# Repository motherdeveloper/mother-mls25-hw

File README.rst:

=====================
Mother MLS12 hardware
=====================

A 12W tunable-white LED driver, powered via PoE.

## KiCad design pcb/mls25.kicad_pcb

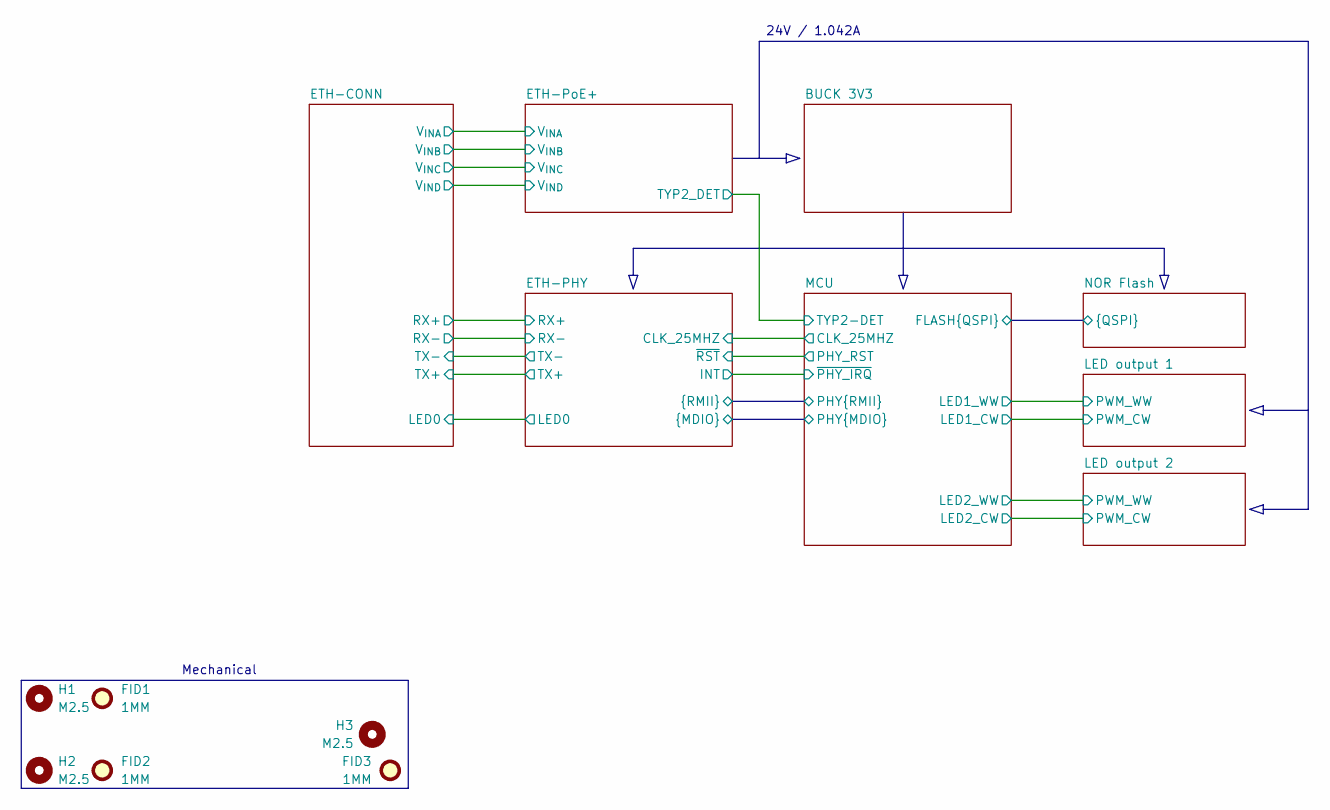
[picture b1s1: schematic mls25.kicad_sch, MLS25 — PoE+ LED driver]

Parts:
FID1, FID2, FID3: 1MM; Fiducial_1mm_Mask2mm
H1, H2, H3: M2.5; MountingHole_2.7mm_M2.5_ISO7380

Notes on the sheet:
24V / 1.042A
Mechanical

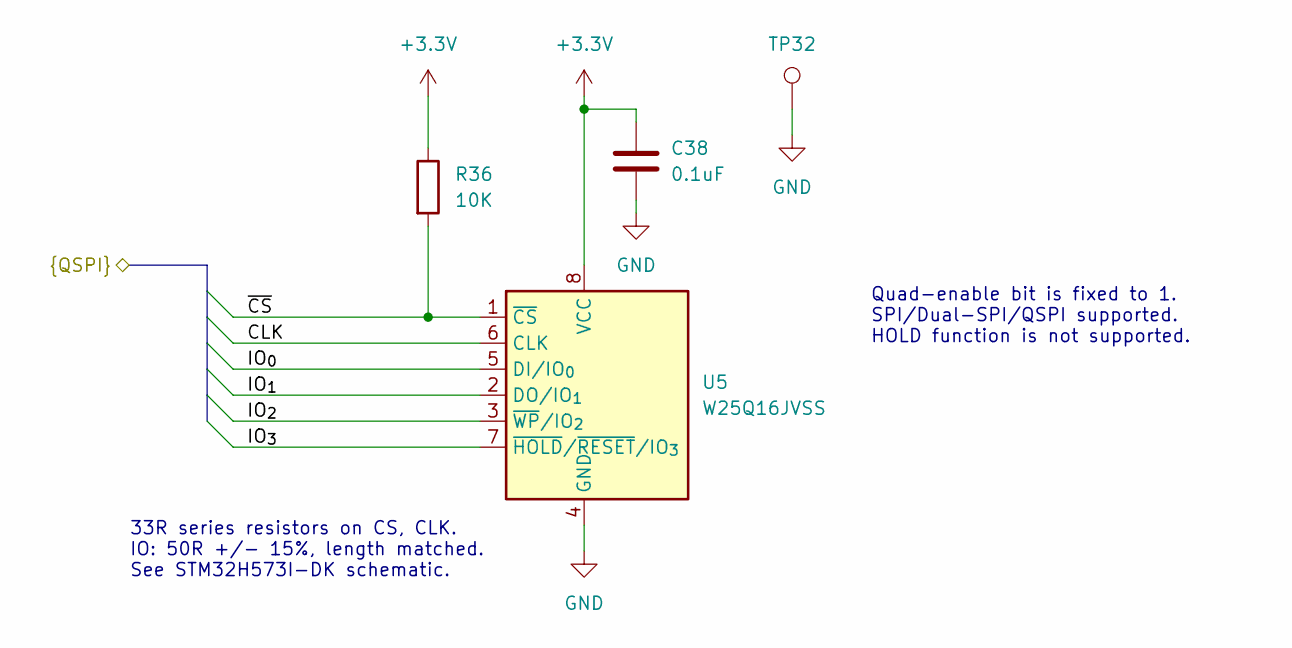
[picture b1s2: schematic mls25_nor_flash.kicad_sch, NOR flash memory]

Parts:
C38: 0.1uF; C_0603_1608Metric; MPN C0603C104M5RACAUTO
R36: 10K; R_0603_1608Metric; MPN AF0603FR-0710KL
TP32: TestPoint; TestPoint_Pad_1.5x1.5mm
U5: W25Q16JVSS; SOIC-8_5.3x5.3mm_P1.27mm; MPN W25Q16JVSSIQ

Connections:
+3.3V: C38.1, R36.1, U5.8 (VCC); also elsewhere on the board
/MCU/FLASH.CLK: U5.6 (CLK); also elsewhere on the board
/MCU/FLASH.IO_{0}: U5.5 (DI/IO_{0}); also elsewhere on the board
/MCU/FLASH.IO_{1}: U5.2 (DO/IO_{1}); also elsewhere on the board
/MCU/FLASH.IO_{2}: U5.3 (~WP/IO_{2}); also elsewhere on the board
/MCU/FLASH.IO_{3}: U5.7 (~HOLD/~RESET/IO_{3}); also elsewhere on the board
/MCU/FLASH.~CS: R36.2, U5.1 (~CS); also elsewhere on the board
GND: C38.2, TP32.1, U5.4 (GND); also elsewhere on the board

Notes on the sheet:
33R series resistors on CS, CLK. IO: 50R +/- 15%, length matched. See STM32H573I-DK schematic.
Quad-enable bit is fixed to 1. SPI/Dual-SPI/QSPI supported. HOLD function is not supported.

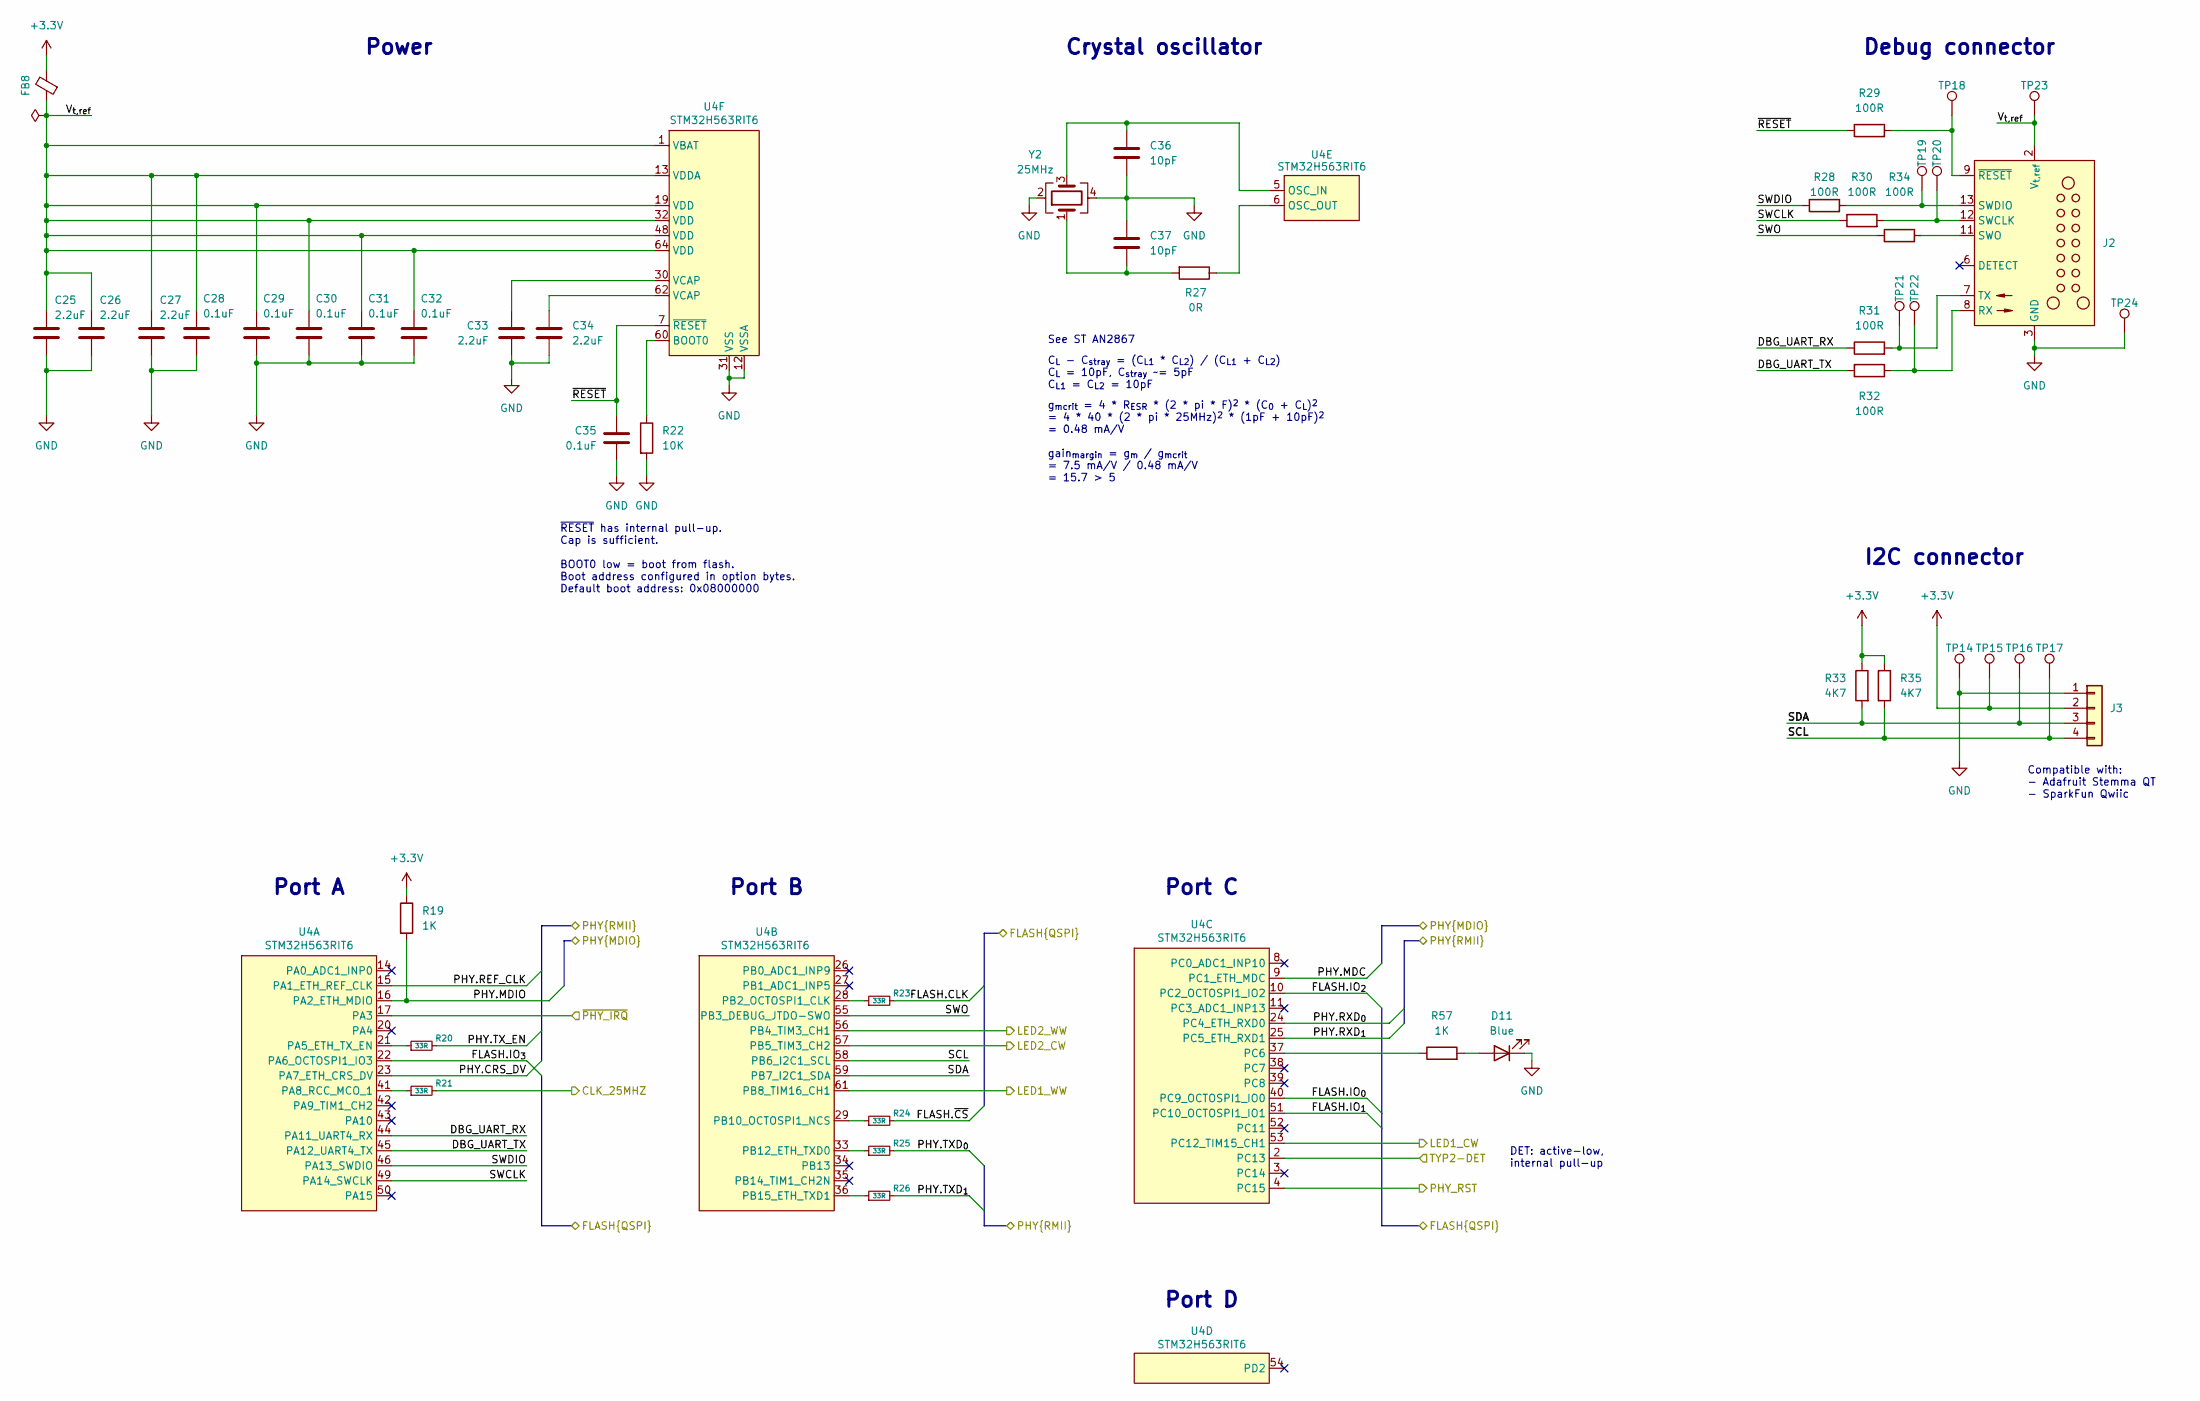
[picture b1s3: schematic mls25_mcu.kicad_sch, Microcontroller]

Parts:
C25, C26, C27, C33, C34: 2.2uF; C_0603_1608Metric; MPN CL10A225KQ8NNNC
C28, C29, C30, C31, C32, C35: 0.1uF; C_0603_1608Metric; MPN C0603C104M5RACAUTO
C36, C37: 10pF; C_0603_1608Metric; MPN 0603N100J100CT
D11: Blue; LED_0603_1608Metric; MPN LTST-C193TBKT-5A
FB8: FerriteBead_Small; L_0805_2012Metric; MPN MPZ2012S102AT000
J2: TC2070-FP; Tag-Connect_TC2070-IDC-FP_2x07_P1.27mm_Vertical; MPN TC2070-IDC-FP
J3: SM04B-SRSS-TB; JST_SH_SM04B-SRSS-TB_1x04-1MP_P1.00mm_Horizontal; MPN SM04B-SRSS-TB
R19, R57: 1K; R_0603_1608Metric; MPN AC0603JR-131KL
R20, R21, R23, R24, R25, R26: 33R; R_0603_1608Metric; MPN WR06X330 JTL
R22: 10K; R_0603_1608Metric; MPN AF0603FR-0710KL
R27: 0R; R_0603_1608Metric; MPN RC0603JR-100RL
R28, R29, R30, R31, R32, R34: 100R; R_0603_1608Metric; MPN RC0603JR-10100RL
R33, R35: 4K7; R_0603_1608Metric; MPN RC0603JR-134K7L
TP14, TP24: TestPoint; TestPoint_Pad_1.5x1.5mm
TP15, TP16, TP17, TP18, TP19, TP20, TP21, TP22, TP23: TestPoint; TestPoint_Pad_D1.5mm
U4: STM32H563RIT6; LQFP-64_10x10mm_P0.5mm; MPN STM32H563RIT6
Y2: 25MHz; Crystal_SMD_3225-4Pin_3.2x2.5mm; MPN CX3225FB25000F0FZZH1

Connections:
+3.3V: FB8.2, J3.2, R19.1, R33.1, R35.1, TP15.1; also elsewhere on the board
/ETH-PHY/CLK_25MHZ: R21.2; also elsewhere on the board
/ETH-PHY/CRS_DV: U4.23 (PA7_ETH_CRS_DV); also elsewhere on the board
/ETH-PHY/INT: U4.17 (PA3); also elsewhere on the board
/ETH-PHY/MDC: U4.9 (PC1_ETH_MDC); also elsewhere on the board
/ETH-PHY/MDIO: R19.2, U4.16 (PA2_ETH_MDIO); also elsewhere on the board
/ETH-PHY/REF_CLK: U4.15 (PA1_ETH_REF_CLK); also elsewhere on the board
/ETH-PHY/RXD_{0}: U4.24 (PC4_ETH_RXD0); also elsewhere on the board
/ETH-PHY/RXD_{1}: U4.25 (PC5_ETH_RXD1); also elsewhere on the board
/ETH-PHY/TXD_{0}: R25.2; also elsewhere on the board
/ETH-PHY/TXD_{1}: R26.2; also elsewhere on the board
/ETH-PHY/TX_EN: R20.2; also elsewhere on the board
/ETH-PHY/~RST: U4.4 (PC15); also elsewhere on the board
/ETH-PoE+/TYP2_DET: U4.2 (PC13); also elsewhere on the board
/LED output 1/PWM_CW: U4.53 (PC12_TIM15_CH1); also elsewhere on the board
/LED output 1/PWM_WW: U4.61 (PB8_TIM16_CH1); also elsewhere on the board
/LED output 2/PWM_CW: U4.57 (PB5_TIM3_CH2); also elsewhere on the board
/LED output 2/PWM_WW: U4.56 (PB4_TIM3_CH1); also elsewhere on the board
/MCU/DBG_UART_RX: R31.1, U4.44 (PA11_UART4_RX)
/MCU/DBG_UART_TX: R32.2, U4.45 (PA12_UART4_TX)
/MCU/FLASH.CLK: R23.2; also elsewhere on the board
/MCU/FLASH.IO_{0}: U4.40 (PC9_OCTOSPI1_IO0); also elsewhere on the board
/MCU/FLASH.IO_{1}: U4.51 (PC10_OCTOSPI1_IO1); also elsewhere on the board
/MCU/FLASH.IO_{2}: U4.10 (PC2_OCTOSPI1_IO2); also elsewhere on the board
/MCU/FLASH.IO_{3}: U4.22 (PA6_OCTOSPI1_IO3); also elsewhere on the board
/MCU/FLASH.~CS: R24.2; also elsewhere on the board
/MCU/SCL: J3.4, R35.2, TP17.1, U4.58 (PB6_I2C1_SCL)
/MCU/SDA: J3.3, R33.2, TP16.1, U4.59 (PB7_I2C1_SDA)
/MCU/SWCLK: R30.1, U4.49 (PA14_SWCLK)
/MCU/SWDIO: R28.1, U4.46 (PA13_SWDIO)
/MCU/SWO: R34.1, U4.55 (PB3_DEBUG_JTDO-SWO)
/MCU/V_{t,ref}: C25.1, C26.1, C27.1, C28.1, C29.1, C30.1, C31.1, C32.1, FB8.1, J2.2 (V_{t,ref}), TP23.1, U4.1 (VBAT), U4.13 (VDDA), U4.19 (VDD), U4.32 (VDD), U4.48 (VDD), U4.64 (VDD)
/MCU/~RESET: C35.1, R29.1, U4.7 (~RESET)
GND: C25.2, C26.2, C27.2, C28.2, C29.2, C30.2, C31.2, C32.2, C33.2, C34.2, C35.2, C36.2, C37.1, D11.1 (K), J2.3 (GND), J2.4 (GND), J3.1, R22.2, TP14.1, TP24.1, U4.12 (VSSA), U4.18 (VSSA), U4.31 (VSS), U4.47 (VSS), U4.63 (VSS), Y2.2, Y2.4; also elsewhere on the board
unnamed: C33.1, U4.30 (VCAP)
unnamed: C34.1, U4.62 (VCAP)
unnamed: C37.2, R27.2, Y2.1
unnamed: D11.2 (A), R57.2
unnamed: J2.8 (RX), R32.1, TP22.1
unnamed: J2.12 (SWCLK), R30.2, TP20.1
unnamed: J2.13 (SWDIO), R28.2, TP19.1
unnamed: J2.11 (SWO), R34.2
unnamed: J2.7 (TX), R31.2, TP21.1
unnamed: J2.9 (~RESET), R29.2, TP18.1
unnamed: R20.1, U4.21 (PA5_ETH_TX_EN)
unnamed: R21.1, U4.41 (PA8_RCC_MCO_1)
unnamed: R23.1, U4.28 (PB2_OCTOSPI1_CLK)
unnamed: R24.1, U4.29 (PB10_OCTOSPI1_NCS)
unnamed: R25.1, U4.33 (PB12_ETH_TXD0)
unnamed: R26.1, U4.36 (PB15_ETH_TXD1)
unnamed: R57.1, U4.37 (PC6)
unnamed: C36.1, U4.5 (OSC_IN), Y2.3
unnamed: R27.1, U4.6 (OSC_OUT)
unnamed: R22.1, U4.60 (BOOT0)

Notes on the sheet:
C_{L} - C_{stray} = (C_{L1} * C_{L2}) / (C_{L1} + C_{L2}) C_{L} = 10pF, C_{stray} ~= 5pF C_{L1} = C_{L2} = 10pF
See ST AN2867
I2C connector
g_{mcrit} = 4 * R_{ESR} * (2 * pi * F)^{2} * (C_{0} + C_{L})^{2} = 4 * 40 * (2 * pi * 25MHz)^{2} * (1pF + 10pF)^{2} = 0.48 mA/V gain_{margin} = g_{m} / g_{mcrit} = 7.5 mA/V / 0.48 mA/V = 15.7 > 5
Debug connector
Crystal oscillator
Power
Port A
Compatible with: - Adafruit Stemma QT - SparkFun Qwiic
Port D
Port C
Port B
DET: active-low, internal pull-up
~{RESET} has internal pull-up. Cap is sufficient. BOOT0 low = boot from flash. Boot address configured in option bytes. Default boot address: 0x08000000

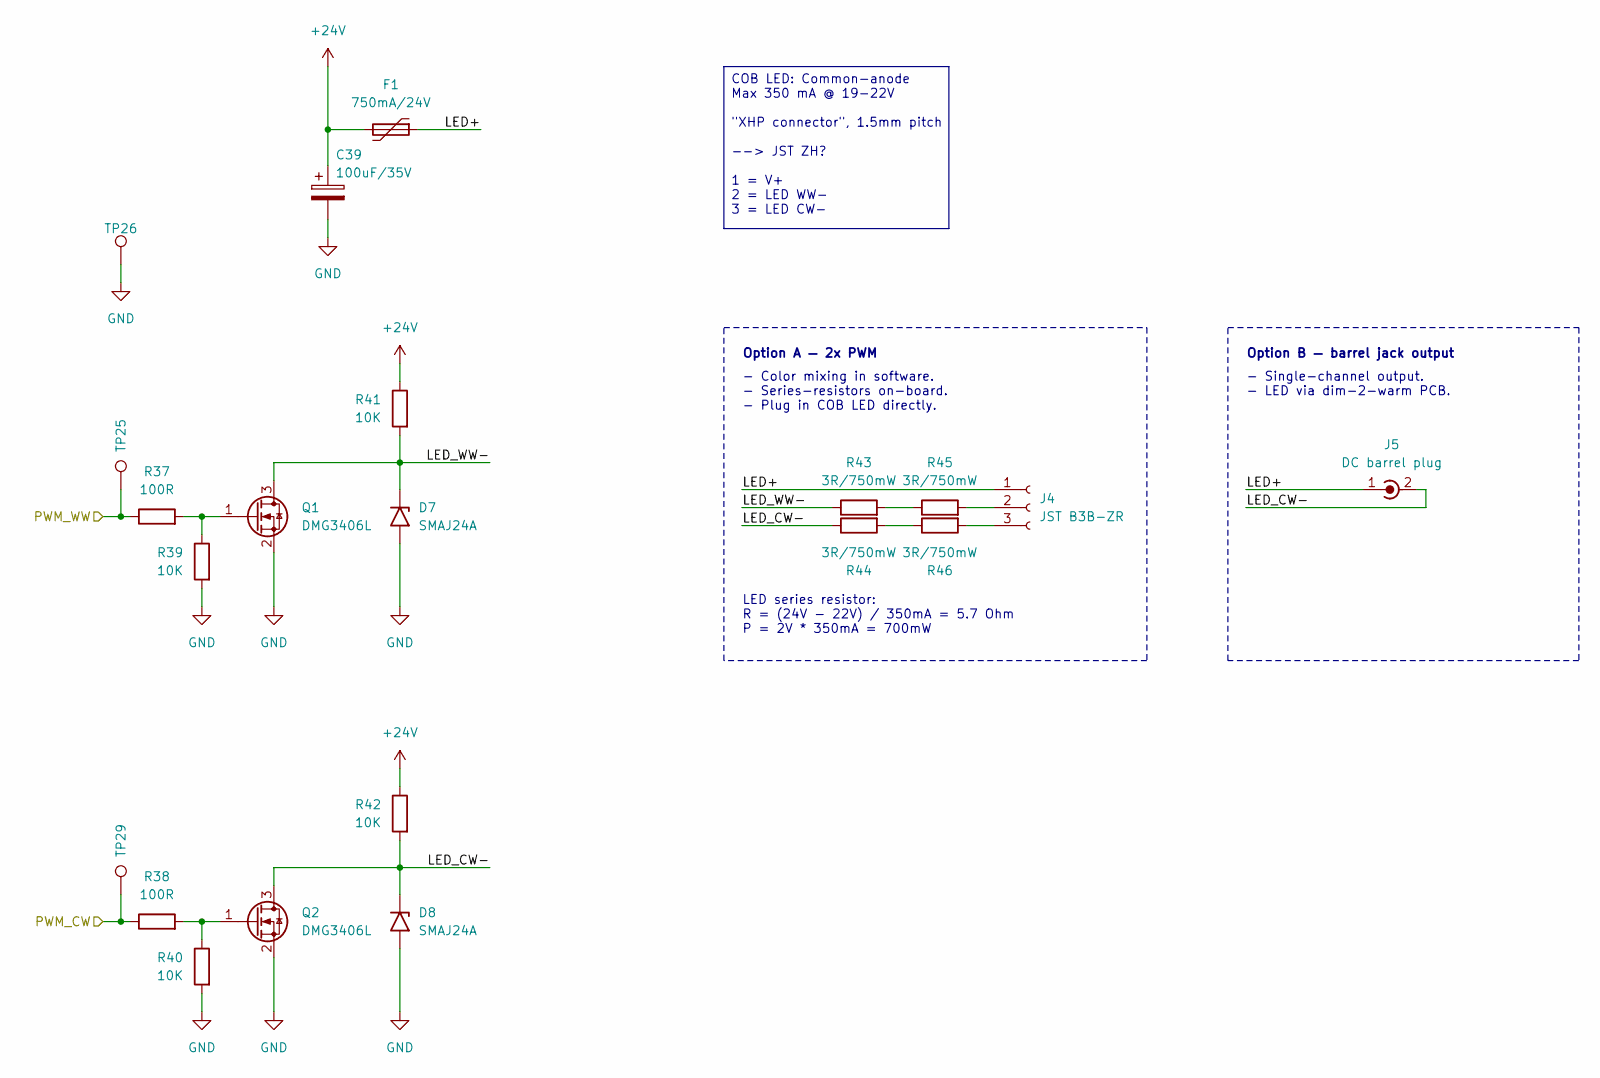
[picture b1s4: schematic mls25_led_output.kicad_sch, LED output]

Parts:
C39: 100uF/35V; CP_Elec_6.3x5.9; MPN 865080545012
D7, D8: SMAJ24A; D_SMA; MPN SMBJ24A/TR13
F1: 750mA/24V; SMD1812B050TF_30; MPN SMD1812B075TF/24
J4: JST B3B-ZR; JST_ZH_B3B-ZR_1x03_P1.50mm_Vertical; MPN B3B-ZR
J5: DC barrel plug; DC_Barrel_Plug_2.1x5.5mm
Q1, Q2: DMG3406L; SOT-23; MPN DMG3406L-13
R37, R38: 100R; R_0603_1608Metric; MPN RC0603JR-10100RL
R39, R40, R41, R42: 10K; R_0603_1608Metric; MPN AF0603FR-0710KL
R43, R44, R45, R46: 3R/750mW; R_1206_3216Metric; MPN ESR18EZPF3R00
TP25, TP29: TestPoint; TestPoint_Pad_D1.5mm
TP26: TestPoint; TestPoint_Pad_1.5x1.5mm

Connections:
+24V: C39.1, F1.2, R41.1, R42.1; also elsewhere on the board
/LED output 1/LED+: F1.1, J4.1, J5.1 (In)
/LED output 1/LED_CW-: D8.1 (A1), J5.2 (Ext), Q2.3 (D), R42.2, R44.1
/LED output 1/LED_WW-: D7.1 (A1), Q1.3 (D), R41.2, R43.1
/LED output 1/PWM_CW: R38.1, TP29.1; also elsewhere on the board
/LED output 1/PWM_WW: R37.1, TP25.1; also elsewhere on the board
GND: C39.2, D7.2 (A2), D8.2 (A2), Q1.2 (S), Q2.2 (S), R39.2, R40.2, TP26.1; also elsewhere on the board
unnamed: J4.2, R45.2
unnamed: J4.3, R46.2
unnamed: Q1.1 (G), R37.2, R39.1
unnamed: Q2.1 (G), R38.2, R40.1
unnamed: R43.2, R45.1
unnamed: R44.2, R46.1

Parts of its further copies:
C40: 100uF/35V; CP_Elec_6.3x5.9; MPN 865080545012
D9, D10: SMAJ24A; D_SMA; MPN SMBJ24A/TR13
F2: 750mA/24V; SMD1812B050TF_30; MPN SMD1812B075TF/24
J6: JST B3B-ZR; JST_ZH_B3B-ZR_1x03_P1.50mm_Vertical; MPN B3B-ZR
J7: DC barrel plug; DC_Barrel_Plug_2.1x5.5mm
Q3, Q4: DMG3406L; SOT-23; MPN DMG3406L-13
R47, R48: 100R; R_0603_1608Metric; MPN RC0603JR-10100RL
R49, R50, R51, R52: 10K; R_0603_1608Metric; MPN AF0603FR-0710KL
R53, R54, R55, R56: 3R/750mW; R_1206_3216Metric; MPN ESR18EZPF3R00
TP27, TP30: TestPoint; TestPoint_Pad_D1.5mm
TP28: TestPoint; TestPoint_Pad_1.5x1.5mm

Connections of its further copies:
+24V: C40.1, F2.2, R51.1, R52.1; also elsewhere on the board
/LED output 2/LED+: F2.1, J6.1, J7.1 (In)
/LED output 2/LED_CW-: D10.1 (A1), J7.2 (Ext), Q4.3 (D), R52.2, R54.1
/LED output 2/LED_WW-: D9.1 (A1), Q3.3 (D), R51.2, R53.1
/LED output 2/PWM_CW: R48.1, TP30.1; also elsewhere on the board
/LED output 2/PWM_WW: R47.1, TP27.1; also elsewhere on the board
GND: C40.2, D9.2 (A2), D10.2 (A2), Q3.2 (S), Q4.2 (S), R49.2, R50.2, TP28.1; also elsewhere on the board
unnamed: J6.2, R55.2
unnamed: J6.3, R56.2
unnamed: Q3.1 (G), R47.2, R49.1
unnamed: Q4.1 (G), R48.2, R50.1
unnamed: R53.2, R55.1
unnamed: R54.2, R56.1

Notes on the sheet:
Option A — 2x PWM
- Color mixing in software. - Series-resistors on-board. - Plug in COB LED directly.
LED series resistor: R = (24V - 22V) / 350mA = 5.7 Ohm P = 2V * 350mA = 700mW
Option B — barrel jack output
- Single-channel output. - LED via dim-2-warm PCB.
COB LED: Common-anode Max 350 mA @ 19-22V "XHP connector", 1.5mm pitch --> JST ZH? 1 = V+ 2 = LED WW- 3 = LED CW-

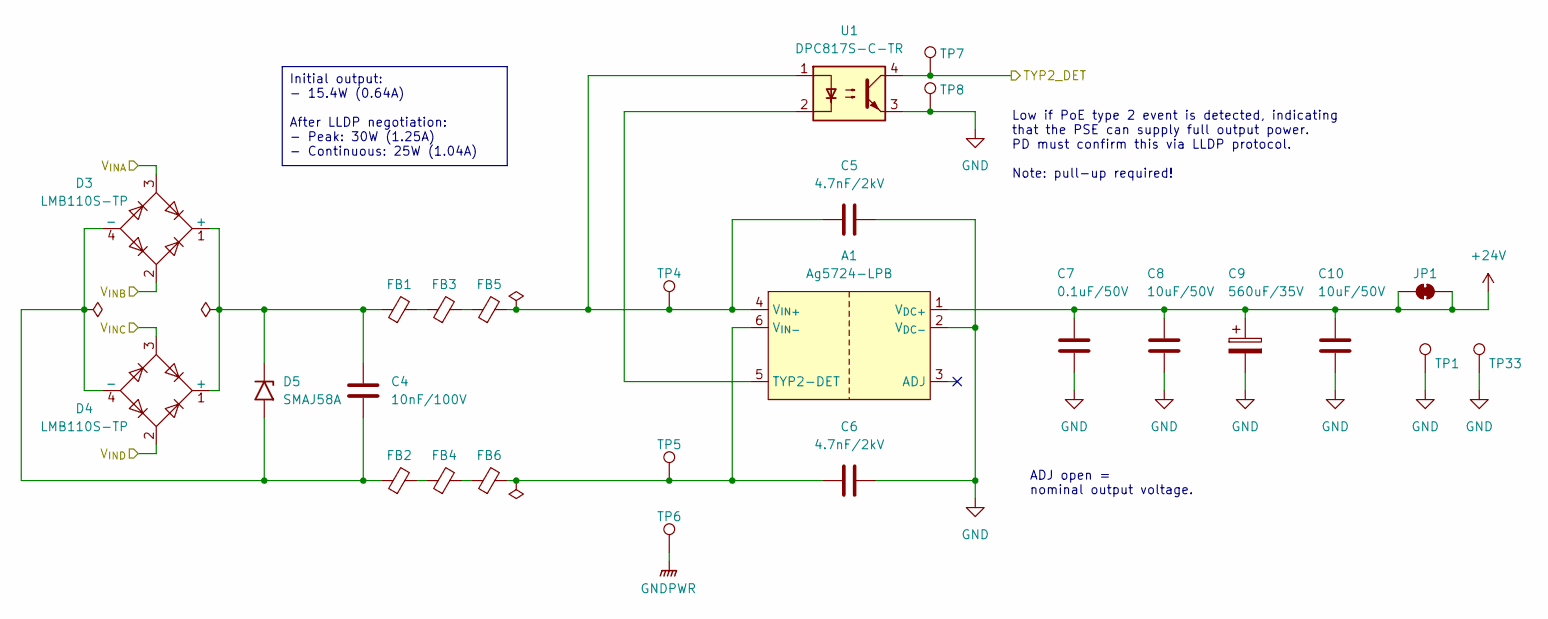
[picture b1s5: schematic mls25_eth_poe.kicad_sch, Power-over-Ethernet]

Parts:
A1: Ag5724-LPB; MPN Ag5724-LPB
C4: 10nF/100V; C_0603_1608Metric; MPN CGA3E2X7R2A103K080AA
C5, C6: 4.7nF/2kV; C_1210_3225Metric; MPN 1210B472K202CT
C7: 0.1uF/50V; C_0603_1608Metric; MPN C0603C104M5RACAUTO
C8, C10: 10uF/50V; C_1206_3216Metric; MPN 1206X106K500CT
C9: 560uF/35V; CP_Elec_10x10.5; MPN EMZS350ARA561MJA0G
D3, D4: LMB110S-TP; MPN LMB110S-TP
D5: SMAJ58A; D_SMA; MPN SMAJ58A/TR13
FB1, FB2, FB3, FB4, FB5, FB6: FerriteBead_Small; L_0805_2012Metric; MPN MPZ2012S102AT000
JP1: SolderJumper_2_Bridged; SolderJumper-2_P1.3mm_Bridged_RoundedPad1.0x1.5mm
TP1, TP6, TP8, TP33: TestPoint; TestPoint_Pad_1.5x1.5mm
TP4, TP5, TP7: TestPoint; TestPoint_Pad_D1.5mm
U1: DPC817S-C-TR; MPN DPC817S-C-TR

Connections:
+24V: A1.1 (V_{DC+}), C7.1, C8.1, C9.1, C10.1, JP1.1 (A), JP1.2 (B); also elsewhere on the board
/ETH-CONN/V_{INA}: D3.3; also elsewhere on the board
/ETH-CONN/V_{INB}: D3.2; also elsewhere on the board
/ETH-CONN/V_{INC}: D4.3; also elsewhere on the board
/ETH-CONN/V_{IND}: D4.2; also elsewhere on the board
/ETH-PoE+/TYP2_DET: TP7.1, U1.4; also elsewhere on the board
GND: A1.2 (V_{DC-}), C5.2, C6.2, C7.2, C8.2, C9.2, C10.2, TP1.1, TP8.1, TP33.1, U1.3; also elsewhere on the board
GNDPWR: TP6.1; also elsewhere on the board
unnamed: A1.5 (TYP2-DET), U1.2
unnamed: A1.4 (V_{IN+}), C5.1, FB5.2, TP4.1, U1.1
unnamed: A1.6 (V_{IN-}), C6.1, FB6.2, TP5.1
unnamed: C4.1, D3.1 (+), D4.1 (+), D5.1 (A1), FB1.1
unnamed: C4.2, D3.4 (-), D4.4 (-), D5.2 (A2), FB2.1
unnamed: FB1.2, FB3.1
unnamed: FB2.2, FB4.1
unnamed: FB3.2, FB5.1
unnamed: FB4.2, FB6.1

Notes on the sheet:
Low if PoE type 2 event is detected, indicating that the PSE can supply full output power. PD must confirm this via LLDP protocol. Note: pull-up required!
ADJ open = nominal output voltage.
Initial output: - 15.4W (0.64A) After LLDP negotiation: - Peak: 30W (1.25A) - Continuous: 25W (1.04A)

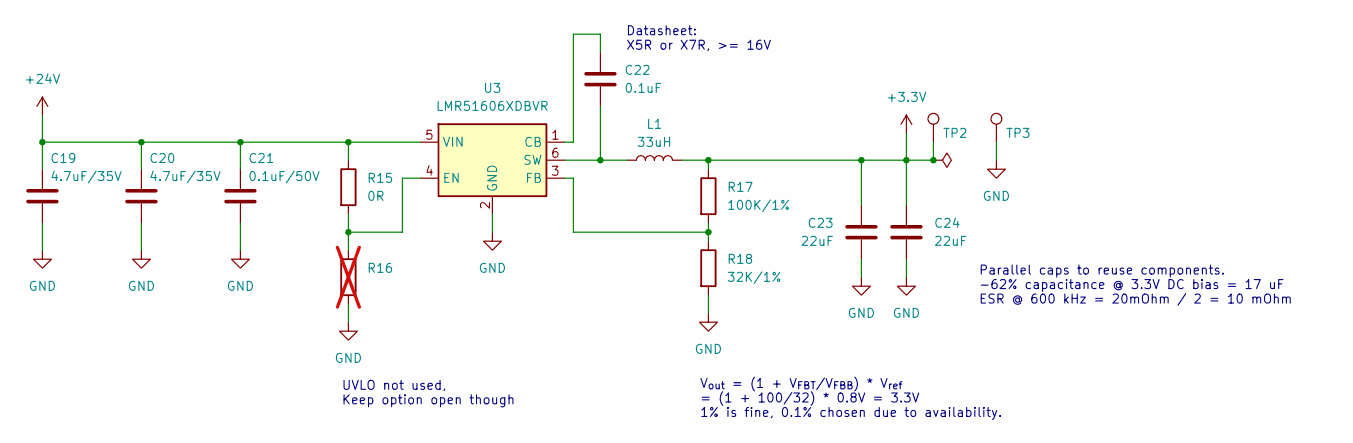
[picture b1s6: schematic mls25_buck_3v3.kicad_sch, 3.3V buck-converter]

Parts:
C19, C20: 4.7uF/35V; C_0603_1608Metric; MPN C1608X5R1V475K080AC
C21: 0.1uF/50V; C_0603_1608Metric; MPN C0603C104M5RACAUTO
C22: 0.1uF; C_0603_1608Metric; MPN C0603C104M5RACAUTO
C23, C24: 22uF; C_0603_1608Metric; MPN GRM188R60J226MEA0J
L1: 33uH; L_Taiyo-Yuden_NR-60xx; MPN NRS6045T330MMGK
R15: 0R; R_0603_1608Metric; MPN RC0603JR-100RL
R16: R_0603_1608Metric; not fitted
R17: 100K/1%; R_0603_1608Metric; MPN RT0603FRE13100KL
R18: 32K/1%; R_0603_1608Metric; MPN RT0603BRD0732KL
TP2: TestPoint; TestPoint_Pad_D1.5mm
TP3: TestPoint; TestPoint_Pad_1.5x1.5mm
U3: LMR51606XDBVR; LMR51606_SOT-23-6; MPN LMR51606XDBVR

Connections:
+3.3V: C23.1, C24.1, L1.2, R17.1, TP2.1; also elsewhere on the board
+24V: C19.1, C20.1, C21.1, R15.1, U3.5 (VIN); also elsewhere on the board
GND: C19.2, C20.2, C21.2, C23.2, C24.2, R16.2, R18.2, TP3.1, U3.2 (GND); also elsewhere on the board
unnamed: C22.1, U3.1 (CB)
unnamed: R15.2, R16.1, U3.4 (EN)
unnamed: R17.2, R18.1, U3.3 (FB)
unnamed: C22.2, L1.1, U3.6 (SW)

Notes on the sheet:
UVLO not used, Keep option open though
Parallel caps to reuse components. -62% capacitance @ 3.3V DC bias = 17 uF ESR @ 600 kHz = 20mOhm / 2 = 10 mOhm
Datasheet: X5R or X7R, >= 16V
V_{out} = (1 + V_{FBT}/V_{FBB}) * V_{ref} = (1 + 100/32) * 0.8V = 3.3V 1% is fine, 0.1% chosen due to availability.

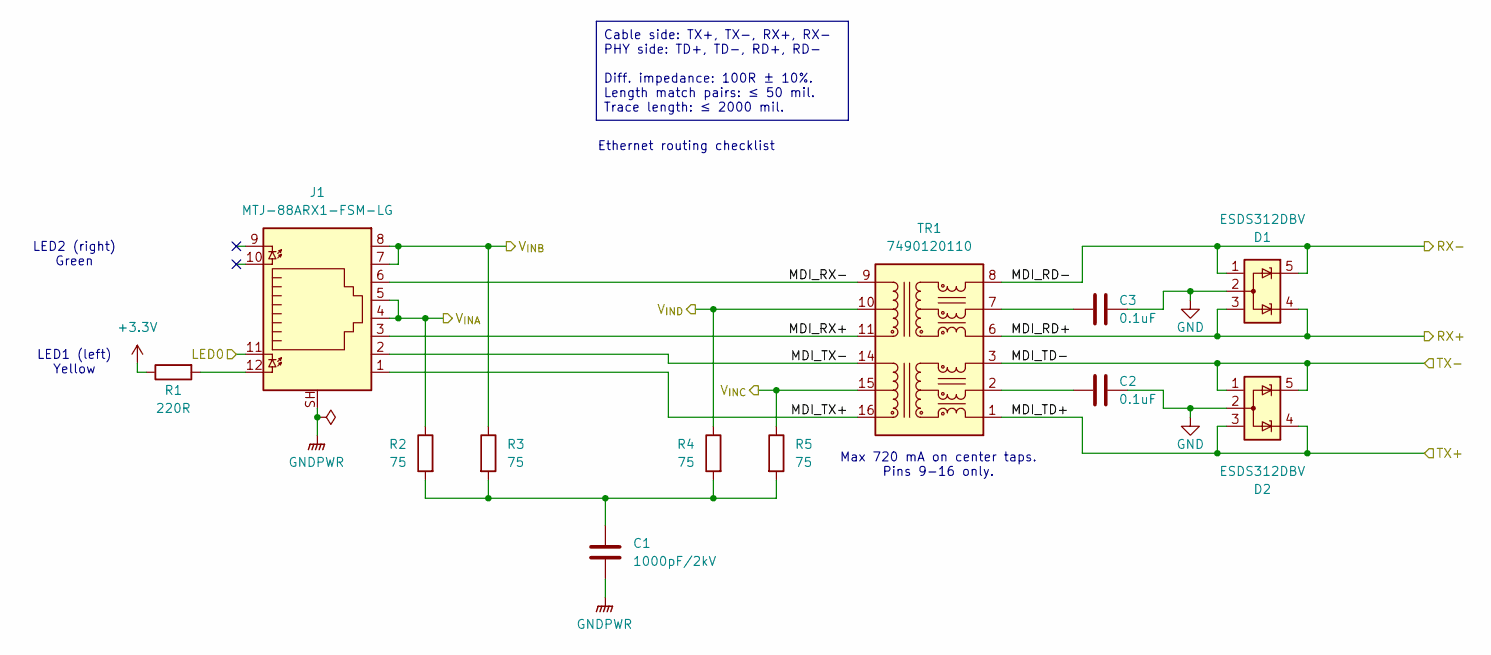
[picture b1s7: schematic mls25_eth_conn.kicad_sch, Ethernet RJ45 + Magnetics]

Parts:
C1: 1000pF/2kV; C_1206_3216Metric; MPN 885342208024
C2, C3: 0.1uF; C_0603_1608Metric; MPN C0603C104M5RACAUTO
D1, D2: ESDS312DBV; SOT-23-5; MPN ESDS312DBVR
J1: MTJ-88ARX1-FSM-LG; RJ45_Amphenol_RJHSE538X; MPN MTJ-88ARX1-FSM-LG
R1: 220R; R_0603_1608Metric; MPN RC0603JR-07220RL
R2, R3, R4, R5: 75; R_0603_1608Metric; MPN WR06X75R0FTL
TR1: 7490120110; MPN 7490120110

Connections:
+3.3V: R1.1; also elsewhere on the board
/ETH-CONN/LED0: J1.11; also elsewhere on the board
/ETH-CONN/MDI_RD+: D1.3 (NC), D1.4 (K), TR1.6 (RD+); also elsewhere on the board
/ETH-CONN/MDI_RD-: D1.1 (NC), D1.5 (K), TR1.8 (RD-); also elsewhere on the board
/ETH-CONN/MDI_RX+: J1.3, TR1.11 (RX+)
/ETH-CONN/MDI_RX-: J1.6, TR1.9 (RX-)
/ETH-CONN/MDI_TD+: D2.3 (NC), D2.4 (K), TR1.1 (TD+); also elsewhere on the board
/ETH-CONN/MDI_TD-: D2.1 (NC), D2.5 (K), TR1.3 (TD-); also elsewhere on the board
/ETH-CONN/MDI_TX+: J1.1, TR1.16 (TX+)
/ETH-CONN/MDI_TX-: J1.2, TR1.14 (TX-)
/ETH-CONN/V_{INA}: J1.4, J1.5, R2.1; also elsewhere on the board
/ETH-CONN/V_{INB}: J1.7, J1.8, R3.1; also elsewhere on the board
/ETH-CONN/V_{INC}: R5.1, TR1.15 (CTX); also elsewhere on the board
/ETH-CONN/V_{IND}: R4.1, TR1.10 (CRX); also elsewhere on the board
GND: C2.2, C3.2, D1.2 (A), D2.2 (A); also elsewhere on the board
GNDPWR: C1.2, J1.SH; also elsewhere on the board
unnamed: C1.1, R2.2, R3.2, R4.2, R5.2
unnamed: J1.12, R1.2
unnamed: C3.1, TR1.7 (CRD)
unnamed: C2.1, TR1.2 (CTD)

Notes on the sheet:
Ethernet routing checklist
Max 720 mA on center taps. Pins 9-16 only.
LED1 (left) Yellow
LED2 (right) Green
Cable side: TX+, TX-, RX+, RX- PHY side: TD+, TD-, RD+, RD- Diff. impedance: 100R ± 10%. Length match pairs: ≤ 50 mil. Trace length: ≤ 2000 mil.

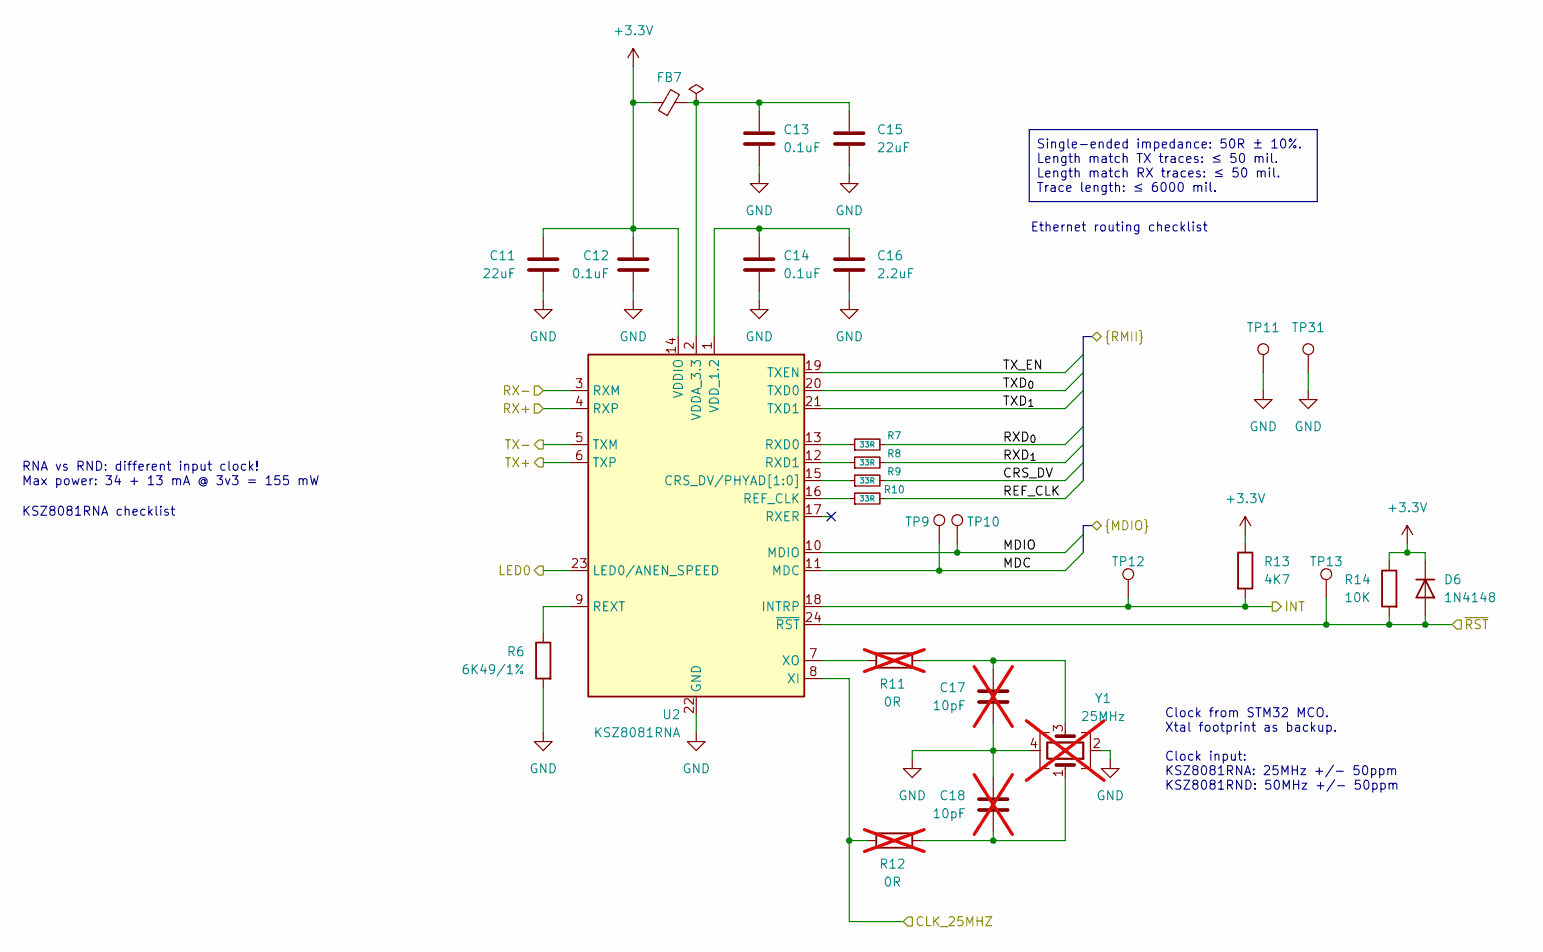
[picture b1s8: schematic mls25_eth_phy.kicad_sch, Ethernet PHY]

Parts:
C11, C15: 22uF; C_0603_1608Metric; MPN GRM188R60J226MEA0J
C12, C13, C14: 0.1uF; C_0603_1608Metric; MPN C0603C104M5RACAUTO
C16: 2.2uF; C_0603_1608Metric; MPN CL10A225KQ8NNNC
C17, C18: 10pF; C_0603_1608Metric; MPN 0603N100J100CT; not fitted
D6: 1N4148; D_SOD-523; MPN 1N4148WT
FB7: FerriteBead_Small; L_0805_2012Metric; MPN MPZ2012S102AT000
R6: 6K49/1%; R_0603_1608Metric; MPN CR0603-FX-6491ELF
R7, R8, R9, R10: 33R; R_0603_1608Metric; MPN WR06X330 JTL
R11, R12: 0R; R_0603_1608Metric; MPN RC0603JR-100RL; not fitted
R13: 4K7; R_0603_1608Metric; MPN RC0603JR-134K7L
R14: 10K; R_0603_1608Metric; MPN AF0603FR-0710KL
TP9, TP10, TP12, TP13: TestPoint; TestPoint_Pad_D1.5mm
TP11, TP31: TestPoint; TestPoint_Pad_1.5x1.5mm
U2: KSZ8081RNA; KSZ8081_QFN-24-1EP_4x4mm_P0.5mm_EP2.6x2.6mm; MPN KSZ8081RNACA
Y1: 25MHz; Crystal_SMD_3225-4Pin_3.2x2.5mm; MPN CX3225FB25000F0FZZH1; not fitted

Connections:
+3.3V: C11.1, C12.1, D6.1 (K), FB7.1, R13.1, R14.1, U2.14 (VDDIO); also elsewhere on the board
/ETH-CONN/LED0: U2.23 (LED0/ANEN_SPEED); also elsewhere on the board
/ETH-CONN/MDI_RD+: U2.4 (RXP); also elsewhere on the board
/ETH-CONN/MDI_RD-: U2.3 (RXM); also elsewhere on the board
/ETH-CONN/MDI_TD+: U2.6 (TXP); also elsewhere on the board
/ETH-CONN/MDI_TD-: U2.5 (TXM); also elsewhere on the board
/ETH-PHY/CLK_25MHZ: R12.1, U2.8 (XI); also elsewhere on the board
/ETH-PHY/CRS_DV: R9.2; also elsewhere on the board
/ETH-PHY/INT: R13.2, TP12.1, U2.18 (INTRP); also elsewhere on the board
/ETH-PHY/MDC: TP9.1, U2.11 (MDC); also elsewhere on the board
/ETH-PHY/MDIO: TP10.1, U2.10 (MDIO); also elsewhere on the board
/ETH-PHY/REF_CLK: R10.2; also elsewhere on the board
/ETH-PHY/RXD_{0}: R7.2; also elsewhere on the board
/ETH-PHY/RXD_{1}: R8.2; also elsewhere on the board
/ETH-PHY/TXD_{0}: U2.20 (TXD0); also elsewhere on the board
/ETH-PHY/TXD_{1}: U2.21 (TXD1); also elsewhere on the board
/ETH-PHY/TX_EN: U2.19 (TXEN); also elsewhere on the board
/ETH-PHY/~RST: D6.2 (A), R14.2, TP13.1, U2.24 (~RST); also elsewhere on the board
GND: C11.2, C12.2, C13.2, C14.2, C15.2, C16.2, C17.2, C18.1, R6.2, TP11.1, TP31.1, U2.22 (GND), U2.25 (GND), Y1.2, Y1.4; also elsewhere on the board
unnamed: C17.1, R11.2, Y1.3
unnamed: C18.2, R12.2, Y1.1
unnamed: R9.1, U2.15 (CRS_DV/PHYAD[1:0])
unnamed: R10.1, U2.16 (REF_CLK)
unnamed: R6.1, U2.9 (REXT)
unnamed: R7.1, U2.13 (RXD0)
unnamed: R8.1, U2.12 (RXD1)
unnamed: C13.1, C15.1, FB7.2, U2.2 (VDDA_3.3)
unnamed: C14.1, C16.1, U2.1 (VDD_1.2)
unnamed: R11.1, U2.7 (XO)

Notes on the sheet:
Ethernet routing checklist
RNA vs RND: different input clock! Max power: 34 + 13 mA @ 3v3 = 155 mW
Clock from STM32 MCO. Xtal footprint as backup. Clock input: KSZ8081RNA: 25MHz +/- 50ppm KSZ8081RND: 50MHz +/- 50ppm
KSZ8081RNA checklist
Single-ended impedance: 50R ± 10%. Length match TX traces: ≤ 50 mil. Length match RX traces: ≤ 50 mil. Trace length: ≤ 6000 mil.

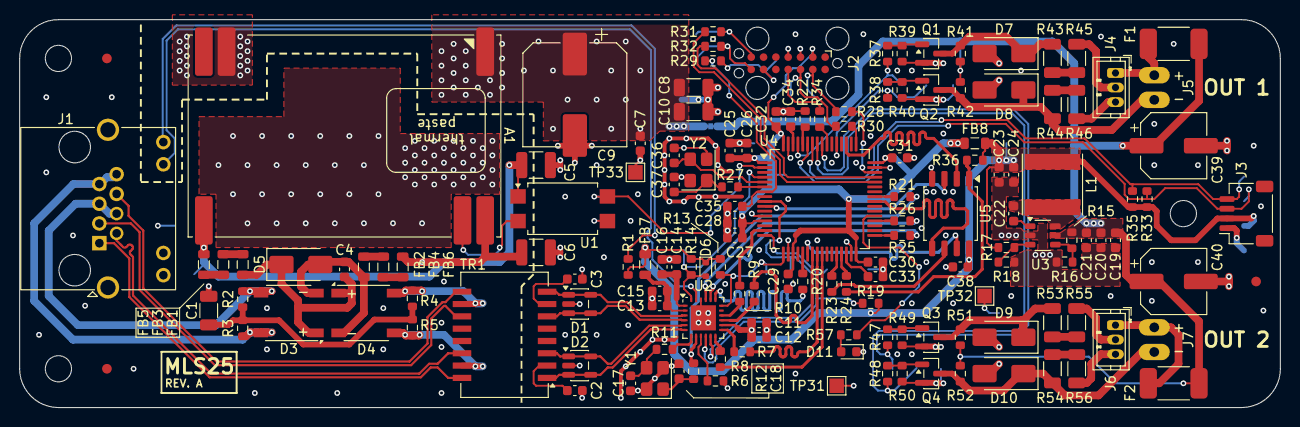
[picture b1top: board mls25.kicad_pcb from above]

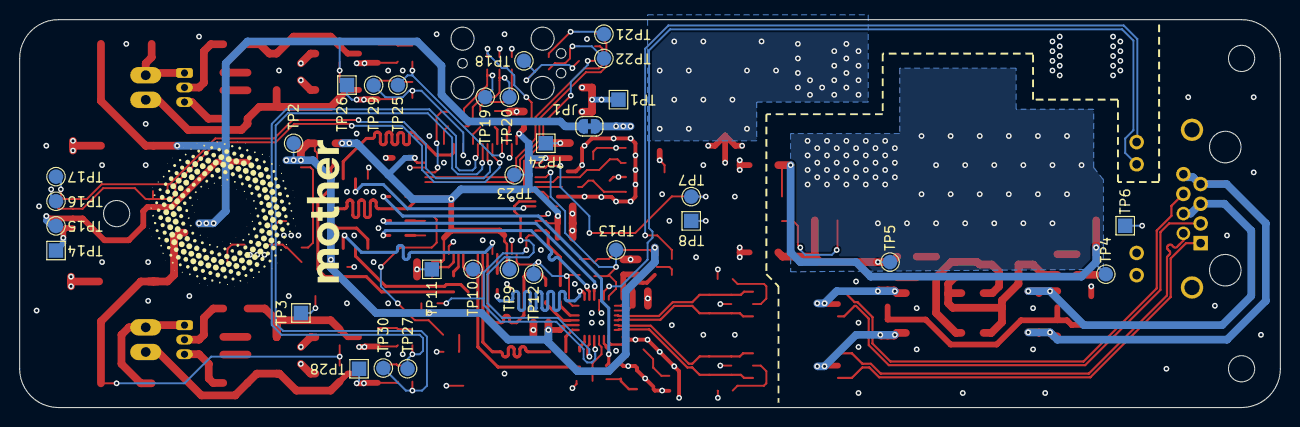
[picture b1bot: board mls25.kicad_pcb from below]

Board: 4 copper layers, 130.0 x 40.0 mm, 179 parts (31 on the bottom side), 114 nets.

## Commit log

2025-07-25 Initial version of MLS12 schematic
2025-07-26 Add LMB110S-TP bridge rectifier
2025-07-26 Add DPC817S-C-TR optocoupler
2025-07-26 Update to 25W PoE+ module, 2 outputs
2025-07-30 Fix default footprint for PoE+ magnetics
2025-07-30 Add polyfuse footprint
2025-07-31 Layout LED outputs, I2C connector
2025-08-01 First Ethernet frontend layout
2025-08-02 Allow MDI DPs to be routed through TVS free pins
2025-08-27 Initial RMII, MDIO routing
2025-09-02 Route NOR flash QSPI traces
2025-09-03 Route MCU decoupling caps
2025-09-06 Layout buck converter, position TagConnect
2025-09-06 Add missing connector, inductor STEPs
2025-09-06 Route +24V
2025-09-06 Route +3V3
2025-09-06 Route low-speed signals
2025-09-08 Route PHY +3V3
2025-09-09 Route PHY IRQ
2025-09-09 Adjust QSPI length matching
2025-09-09 Add blinky LED
2025-09-09 Xtal layout, guard rings
2025-09-10 Ground return vias
2025-09-10 Add mounting holes, round corners
2025-09-19 Add power planes, fiducials
2025-09-21 Add test points
2025-09-27 Cleanup silkscreen, add logo
2025-09-27 Rename `mls12` to `mls25`
    Module output was changed from 12W to 25W during the course of development.
    Update filenames to reflect that.
2025-09-30 Fix ERC warnings/errors
    * Add NC-flags to microcontroller pins.
    * Fix STM32 VCAP, ~RESET pin type.
    * Add PWR_FLAG symbols.
2025-10-04 Tweaks/fixes after design review
    * Fix RJ45 refdes on silkscreen.
    * Change PHY IRQ pullup from 1K to 4K7 per datasheet recommendations.
    * Add skew correction on MDI TX differential pair.
    * Remove copper under magnetics.
    * Add annotation that TYP2_DET signal requires MCU internal pullup.
2025-10-04 Change PHY to datasheet recommended footprint
    Default footprint in the Kicad libraries for KSZ8081 deviates from the
    datasheet recommendations. QFN parts can be fiddly, so it's best to stick
    closely to the recommendations:
    * Pads are much shorter and a bit thinner.
    * Solder stencil openings for exposed pad are smaller, spaced out a bit less.
2025-10-07 Change output polyfuse from 500mA to 750mA
2025-10-21 Exclude test pads from BOM
2025-10-21 Set origin, change page template, link revision silkscreen to field
2025-10-22 Add full MPN to buck converter IC
2025-10-22 Update Kicad 9.0.5 footprints
2025-10-22 Bump title block date
2025-10-22 Add rev A release files
2025-10-22 Add release jobset
